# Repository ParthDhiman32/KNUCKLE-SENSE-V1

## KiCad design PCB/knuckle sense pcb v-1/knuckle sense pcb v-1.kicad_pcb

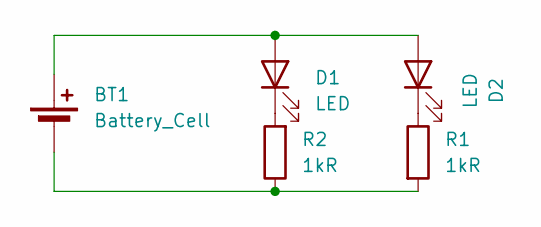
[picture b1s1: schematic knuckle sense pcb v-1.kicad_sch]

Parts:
BT1: Battery_Cell; BatteryHolder_Keystone_3034_1x20mm
D1, D2: LED; LED_D5.0mm
R1, R2: 1kR; R_Axial_DIN0207_L6.3mm_D2.5mm_P7.62mm_Horizontal

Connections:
unnamed: BT1.1 (+), D1.2 (A), D2.2 (A)
unnamed: BT1.2 (-), R1.2, R2.1
unnamed: D1.1 (K), R2.2
unnamed: D2.1 (K), R1.1

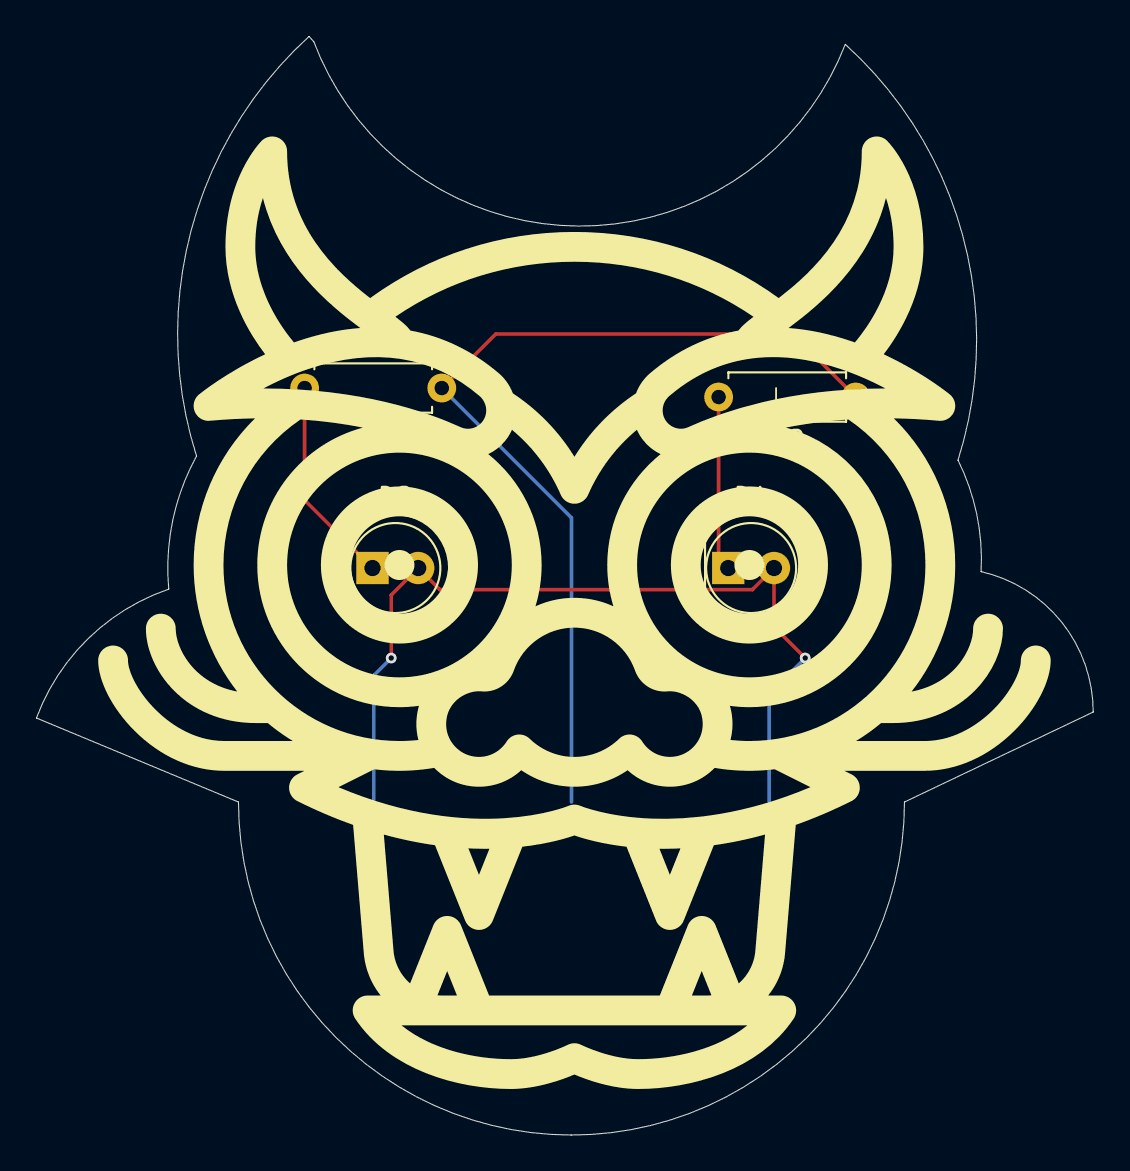
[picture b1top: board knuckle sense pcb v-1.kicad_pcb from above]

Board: 2 copper layers, 58.7 x 61.0 mm, 5 parts (1 on the bottom side), 4 nets.
